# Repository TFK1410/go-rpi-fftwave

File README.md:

# go-rpi-fftwave

## What it is

This is a project for visualizing sound data on Raspberry Pi using LED screens with HUB75 connections and a soundcard.

The required software components are [FFTW3](http://www.fftw.org/), [rpi-rgb-led-matrix](https://github.com/hzeller/rpi-rgb-led-matrix) and portaudio libraries.

This is a rework of the [rpi-sound-c](https://github.com/TFK1410/rpi-sound-c) project. It worked fine on it's own but it was hard for me to maintain. I've used the dev branch of that repository for a while now but I figured it's time for a change.

This repository holds a rework written completely in Go. However it still uses some CGO snippets wherever necessary and it still uses the FFTW3 library as it is much faster than the internal FFT implementation in Go. 

Software includes:
* Display of FFT bins in logarithmic scale with color gradient starting from green at the bottom to red at the top
* White dot scale similar to those seen in Winamp spectrum display which will hold the temporary max value and after some time it will start to fall
* Background coloring based on the sound energy history creating color ripples
* Ability to add more ways of displaying the data and for it to be changed at runtime
* Implementation of a rotary encoder which is used to adjust the brightness of the display, switch the displayed pattern and toggle DMX coloring mode
* I2C communication with an Arduino Nano sidekick which reads incoming DMX data to change the display color via an external DMX sender

## Before running

The go get command will fail for the first time when pulling the necessary libraries. For how to get the Go bindings to work which should resolve those issues I'll refer to the [go-rpi-rgb-led-matrix](https://github.com/TFK1410/go-rpi-rgb-led-matrix) repo.

To be able to run the software next thing should be to also compile the FFTW library on Rasbperry Pi. I refer to the official website for more info on how to compile FFTW http://www.fftw.org/.

Next thing is setting up the default recording interface on the Rasberry Pi. Command like `arecord -l` should be helpful here as well as looking for the topic of blacklisting unneeded sound cards on the RPI.

One thing that also may recommend is isolating the last core from the four available on the RPI. This can improve the performance a little bit especially for the rpi-rgb-led-matrix library functions. This can be accomplished by adding `isolcpus=3 rcu_nocbs=3` at the end of /boot/cmdline.txt of the raspberry and then rebooting it. The isolation should be seen when looking at the content of the /proc/cmdline file:
```
$ cat /proc/cmdline
8250.nr_uarts=1 bcm2708_fb.fbwidth=656 bcm2708_fb.fbheight=416 bcm2708_fb.fbswap=1 vc_mem.mem_base=0x3ec00000 vc_mem.mem_size=0x40000000  dwc_otg.lpm_enable=0 console=ttyAMA0,115200 console=tty1 root=PARTUUID=e968d391-02 rootfstype=ext4 elevator=deadline fsck.repair=yes rootwait isolcpus=3 rcu_nocbs=3
```

## Configuration

An example configuration file with the descriptions on how to use those is provided at the root of this repo: config.yml. Please read through it to find some descriptions for the available options in the application. To use this configuration file use the -c/-config flag.

## Service file

The repository also includes a service file which can be deployed to run the application on boot using systemd.
```sh
sudo cp go-fft-display.service /lib/systemd/system/
sudo systemctl daemon-reload
sudo systemctl enable go-fft-display
sudo systemctl start go-fft-display
```

Change the service file accordingly if the configuration file is stored somewhere else

## Troubleshooting

If you are experiencing issues with PortAudio about it complaining: "cannot find card '0'" or something along those lines there are two things worth trying:
Add your user and maybe also the root user to the audio group
```sh
sudo usermod -a -G audio pi
sudo usermod -a -G audio root
```

Create a modprobe.d file to set the usb sound card at the first index:
```sh
$ cat /etc/modprobe.d/alsa-base.conf
options snd-usb-audio index=0
```

Disable HDMI audio on RPi4 as well for good measure
```sh
$ cat /boot/config.txt
...
#dtoverlay=vc4-kms-v3d
dtoverlay=vc4-kms-v3d,noaudio
...
```

Also if you are at it it might be worth it to add your user to the gpio group as well. This would be used for the rotary encoder. No message will show up if this is causing some issues without being added to the group. The encoder just will not register.
```sh
sudo usermod -a -G gpio pi
sudo usermod -a -G gpio root
sudo usermod -a -G i2c pi
sudo usermod -a -G i2c root
```

## Ansible installation playbooks

TODO

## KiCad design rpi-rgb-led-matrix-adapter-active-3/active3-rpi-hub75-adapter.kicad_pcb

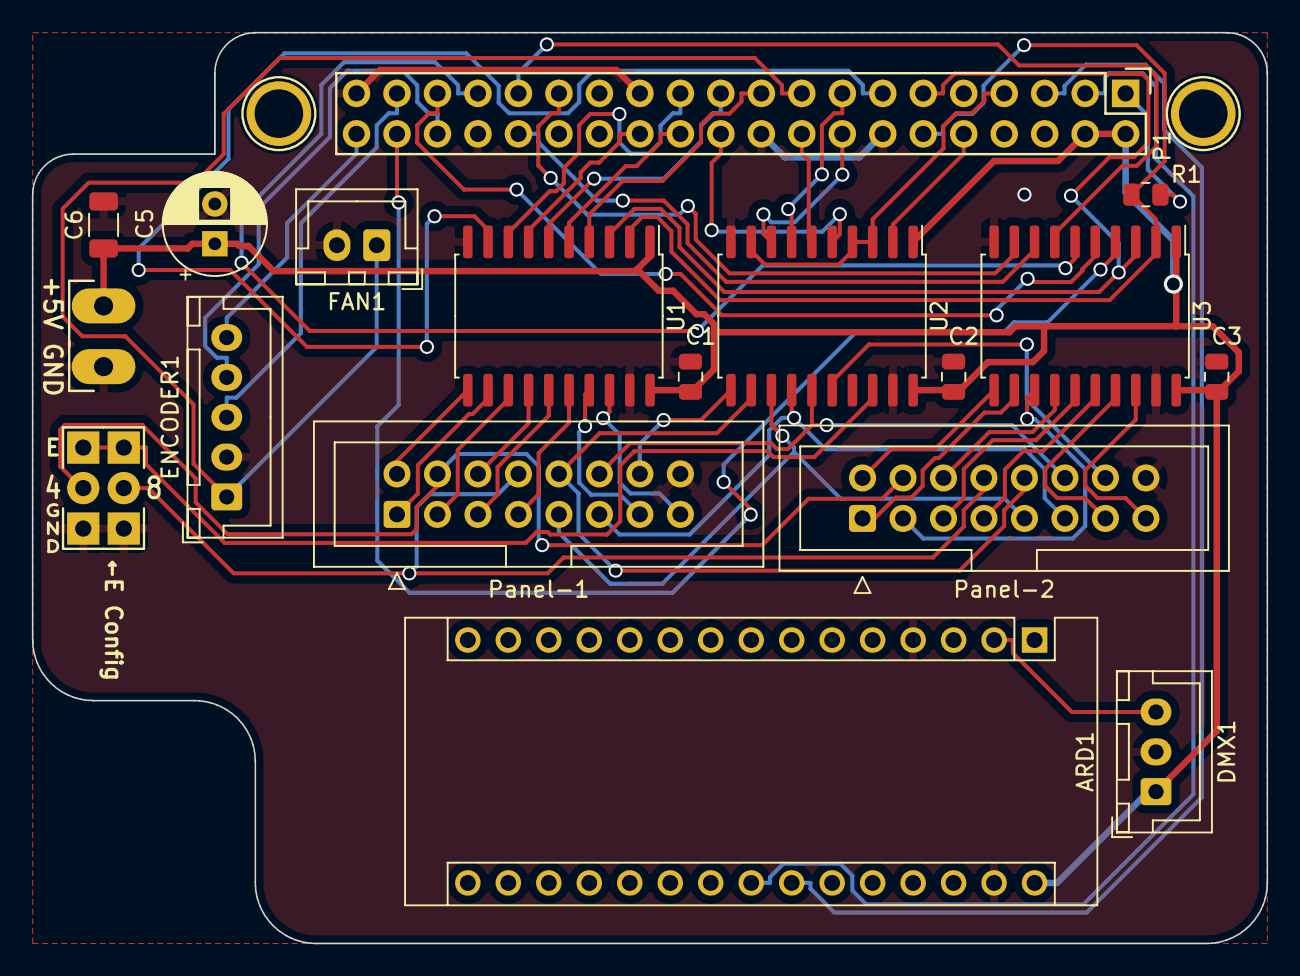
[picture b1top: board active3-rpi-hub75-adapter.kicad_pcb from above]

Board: 2 copper layers, 77.5 x 57.2 mm, 23 parts (0 on the bottom side), 55 nets.

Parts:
ARD1: Arduino_Nano_Every; Arduino_Nano
C1, C2, C3: 100n; C_0805_2012Metric
C5: 22u; CP_Radial_D6.3mm_P2.50mm
C6: 22u; C_1206_3216Metric
DMX1: CONN_01x03; JST_XH_B3B-XH-A_1x03_P2.50mm_Vertical
ENCODER1: CONN_01x05; JST_XH_B5B-XH-A_1x05_P2.50mm_Vertical
FAN1: CONN_01X02; JST_XH_B2B-XH-A_1x02_P2.50mm_Vertical
P1: CONN_02X20; Pin_Header_Straight_2x20
P2: +5V; Pin_Header_Straight_1x01
P4: GND; Pin_Header_Straight_1x01
P6, P8: CONN_01X02; Pin_Header_Straight_1x02
P7: CONN_02X01; Pin_Header_Straight_1x02
P20, P21: CONN_01X01; 1pin
Panel-1, Panel-2: CONN_02X08; IDC-Header_2x08_P2.54mm_Vertical
R1: 10k; R_0805_2012Metric
U1, U2, U3: 74HCT245; SOIC-20W_7.5x12.8mm_P1.27mm

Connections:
3v3: ENCODER1.1, FAN1.1, P1.17
GND: ARD1.4 (GND), ARD1.29 (GND), C1.2, C2.2, C3.2, C5.2, C6.2, DMX1.2, ENCODER1.2, FAN1.2, P1.6, P1.14, P1.20, P1.25, P1.34, P1.39, P4.1, P8.1, P8.2, Panel-1.16, Panel-2.16, U1.10 (GND), U1.19 (CE), U2.10 (GND), U2.19 (CE), U3.10 (GND), U3.19 (CE)
unnamed: P1.1, R1.2
unnamed: P6.1, P6.2, U2.18 (B0)
OE: P1.12, R1.1, U1.2 (A0), U3.2 (A0)
OE_buff_0: Panel-1.15, U1.18 (B0)
OE_buff_1: Panel-2.15, U3.18 (B0)
Sel-Pin4: P7.1, Panel-1.4, Panel-2.4
Sel-Pin8: P7.2, Panel-1.8, Panel-2.8
VCC: ARD1.30 (VIN), C1.1, C2.1, C3.1, C5.1, C6.1, DMX1.1, P1.2, P1.4, P2.1, U1.1 (A->B), U1.20 (VCC), U2.1 (A->B), U2.20 (VCC), U3.1 (A->B), U3.20 (VCC)
clock: P1.11, U1.3 (A1), U3.3 (A1)
clock_buff_0: Panel-1.13, U1.17 (B1)
clock_buff_1: Panel-2.13, U3.17 (B1)
dmx_rx: ARD1.2 (RX1), DMX1.3
enc_clk: ENCODER1.5, P1.40
enc_dt: ENCODER1.4, P1.36
enc_sw: ENCODER1.3, P1.37
i2c1_scl: ARD1.24 (SCL/A5), P1.5
i2c1_sda: ARD1.23 (SDA/A4), P1.3
p0_b1: P1.26, U1.7 (A5)
p0_b1_buff: Panel-1.3, U1.13 (B5)
p0_b2: P1.19, U1.4 (A2)
p0_b2_buff: Panel-1.7, U1.16 (B2)
p0_g1: P1.13, U1.9 (A7)
p0_g1_buff: Panel-1.2, U1.11 (B7)
p0_g2: P1.21, U1.6 (A4)
p0_g2_buff: Panel-1.6, U1.14 (B4)
p0_r1: P1.23, U1.8 (A6)
p0_r1_buff: Panel-1.1, U1.12 (B6)
p0_r2: P1.24, U1.5 (A3)
p0_r2_buff: Panel-1.5, U1.15 (B3)
p1_b1: P1.31, U3.7 (A5)
p1_b1_buff: Panel-2.3, U3.13 (B5)
p1_b2: P1.38, U3.4 (A2)
p1_b2_buff: Panel-2.7, U3.16 (B2)
p1_g1: P1.29, U3.9 (A7)
p1_g1_buff: Panel-2.2, U3.11 (B7)
p1_g2: P1.33, U3.6 (A4)
p1_g2_buf: Panel-2.6, U3.14 (B4)
p1_r1: P1.32, U3.8 (A6)
p1_r1_buff: Panel-2.1, U3.12 (B6)
p1_r2: P1.35, U3.5 (A3)
p1_r2_buff: Panel-2.5, U3.15 (B3)
row_A: P1.15, U2.7 (A5)
row_A_buff: Panel-1.9, Panel-2.9, U2.13 (B5)
row_B: P1.16, U2.8 (A6)
row_B_buff: Panel-1.10, Panel-2.10, U2.12 (B6)
row_C: P1.18, U2.6 (A4)
row_C_buff: Panel-1.11, Panel-2.11, U2.14 (B4)
row_D: P1.22, U2.5 (A3)
row_D_buff: Panel-1.12, Panel-2.12, U2.15 (B3)
row_E: P1.10, U2.2 (A0)
strobe: P1.7, U2.3 (A1), U2.4 (A2), U2.9 (A7)
strobe_buff_0: Panel-1.14, U2.11 (B7)
strobe_buff_1: Panel-2.14, U2.16 (B2)

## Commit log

2020-02-20 Adding empty go.mod
2020-02-29 Wrote recording part of the application
2020-02-29 Created a basic FFT thread
2020-02-29 Continued the work on the output raw logarithmic FFT data
2020-02-29 First data displayed
2020-03-02 Implemented white dot, color gradient and the base for sound energy display
2020-03-03 Implemented sound energy wave drawing
2020-03-03 Added the code around the rotary encoder
2020-03-06 Simplified the goroutine creation and closing process
2020-03-06 Implemented most of the encoder message sending
2020-03-06 Sound energy wave is now in HSV hue color :)
2020-03-08 Made the goroutine setup a bit cleaner
2020-03-08 Added configuration ingest
2020-03-08 Started to work on the DMX reader, haven't tested yet
2020-03-08 Added the long press DMX mode switch functionality
2020-03-08 Implemented another wave type and the selection using the encoder
2020-03-08 Created dual width wave pattern
2020-03-09 One more new pattern
2020-03-09 Added simple config flag
2020-03-09 Included a template service file
2020-03-09 Added comments to the configuration file
2020-03-09 Added comments to code and started with some empty files right now for ansible playbooks
2020-03-09 Added links to libraries
2020-03-09 Added a gif :)
2020-03-12 Small fixes to the DMX reader module after testing it with Rekordbox
2020-03-14 Added arduino sketch to the repo along with a small code adjustment
2020-04-05 Renamed arduino sketch path
2020-04-05 A significant update adding a lyrics module to the application which allows for the display of song lyrics
2020-04-07 Started to work on options for each lyric line with <> marks, right now added support for dynamic font size
2021-04-02 Project refresh initial commit with dependecies update
2021-04-05 Significant update after coming back to the project, reworked the lyrics module and added new dmx parameters
2021-04-09 Replaced embd package as it is not being updated with periph
2021-04-09 Simplified the lyric image overlay function instead of using the builtin draw as it took too long around 6ms each time
2021-04-18 Lyricsoverlay update after some live tests, missed the w letter initially
2021-04-18 Some bugfixes with lyrics part while expermienting
2021-04-19 More bugfixes and reworks for the lyrics
2021-04-19 Implemented color palette offset wrapping
2021-10-29 Reversed palette index orders
2021-12-30 Redesigned the background waves to be a separate module with different possible effects
2022-02-07 Update after the migration to 64-bit system
2022-02-23 Reworked the encoder to have DMX always active
2022-02-23 Added two new background patterns that modify the front wave color
2022-06-09 Added a missing line to the press function of the encoder
2022-07-04 Added adapter schematics
2022-07-04 Moved other test projects into the repository
2022-08-19 DMX and pixelfont fixes
2022-08-19 Background mode from DMX had a typo
2022-08-20 Moved background canvas generation to the phase before the lyrics display
2022-08-22 Fixed a bug where I scaled down the bar heights twice in the drawloops
2023-03-21 Library updates
2023-03-21 Updated how the short bins are handled
2023-04-11 Updated the general drawloop implementation, disconnected the code from the hard coded bin size, added single column wave pattern
